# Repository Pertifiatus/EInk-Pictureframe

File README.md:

# E-Ink Picture Frame

A battery-powered **color e-paper picture frame** that rotates itself between portrait and landscape. Pictures are uploaded and managed in a web interface hosted by the frame itself.

## Features

- **7.3" Spectra 6 e-paper** (GDEP073E01, 800×480, 6 colors). It keeps the image without using power.
- **Motorized rotation:** a 28BYJ-48 stepper with a 40:1 worm gear turns the frame by 90°. An IMU (MPU-9250) detects the orientation and fine-tunes the position.
- **Built-in web app:** the frame opens its own WiFi access point (`http://192.168.4.1`) where you can:
  - upload and delete pictures (thumbnails are generated automatically)
  - create playlists and pick the current picture
  - set the clock, change settings, calibrate the motor
- **Deep sleep:** the DS3231 RTC wakes the frame to change the picture. A button wakes it up to start the WiFi interface.
- Battery monitoring with a low-battery indicator on the picture, plus an RGB status LED.
- Images, playlists and settings are stored on a microSD card.

## Hardware

| Part | Details |
|---|---|
| MCU | ESP32-S3 (with PSRAM) |
| Display | GDEP073E01 via DESPI-C02 adapter (SPI) |
| Storage | microSD (shares the SPI bus) |
| RTC / IMU | DS3231 + MPU-9250 (I2C) |
| Motor | 28BYJ-48 + ULN2003, worm gear 40:1 |
| Power | Li-ion battery |
| PCB | Custom KiCad board (`Ki-Cad/EInk-Rahmen`) |

All pins are defined in `config.h`.

## Repository structure

```
Arduino/
  eink_frame_V11/       Latest firmware (config.h, display/motor modules, web UI)
  eink_frame_V2..V10/   Earlier versions / milestones
  eink_frame_V10_WOmotor/  Variant without rotation motor
  Test/                 Hardware tests (display, SD, I2C scanner, LED, stepper)
3D Files/Frame.f3z      Fusion 360 frame model
Ki-Cad/EInk-Rahmen/     Schematic and PCB
```

## Getting started

1. Install these libraries: **GxEPD2**, **ESPAsyncWebServer** + **AsyncTCP** (mathieucarbou), **RTClib**, **AccelStepper**.
2. Board: *ESP32S3 Dev Module* with PSRAM enabled.
3. Copy `eink_frame.html` to the SD card as `/index.html` and create an `/images` folder.
4. Adjust the WiFi name/password in `config.h`, then upload `eink_frame_V11.ino`.
5. Press the WiFi button, connect to the frame's network and open `http://192.168.4.1`.

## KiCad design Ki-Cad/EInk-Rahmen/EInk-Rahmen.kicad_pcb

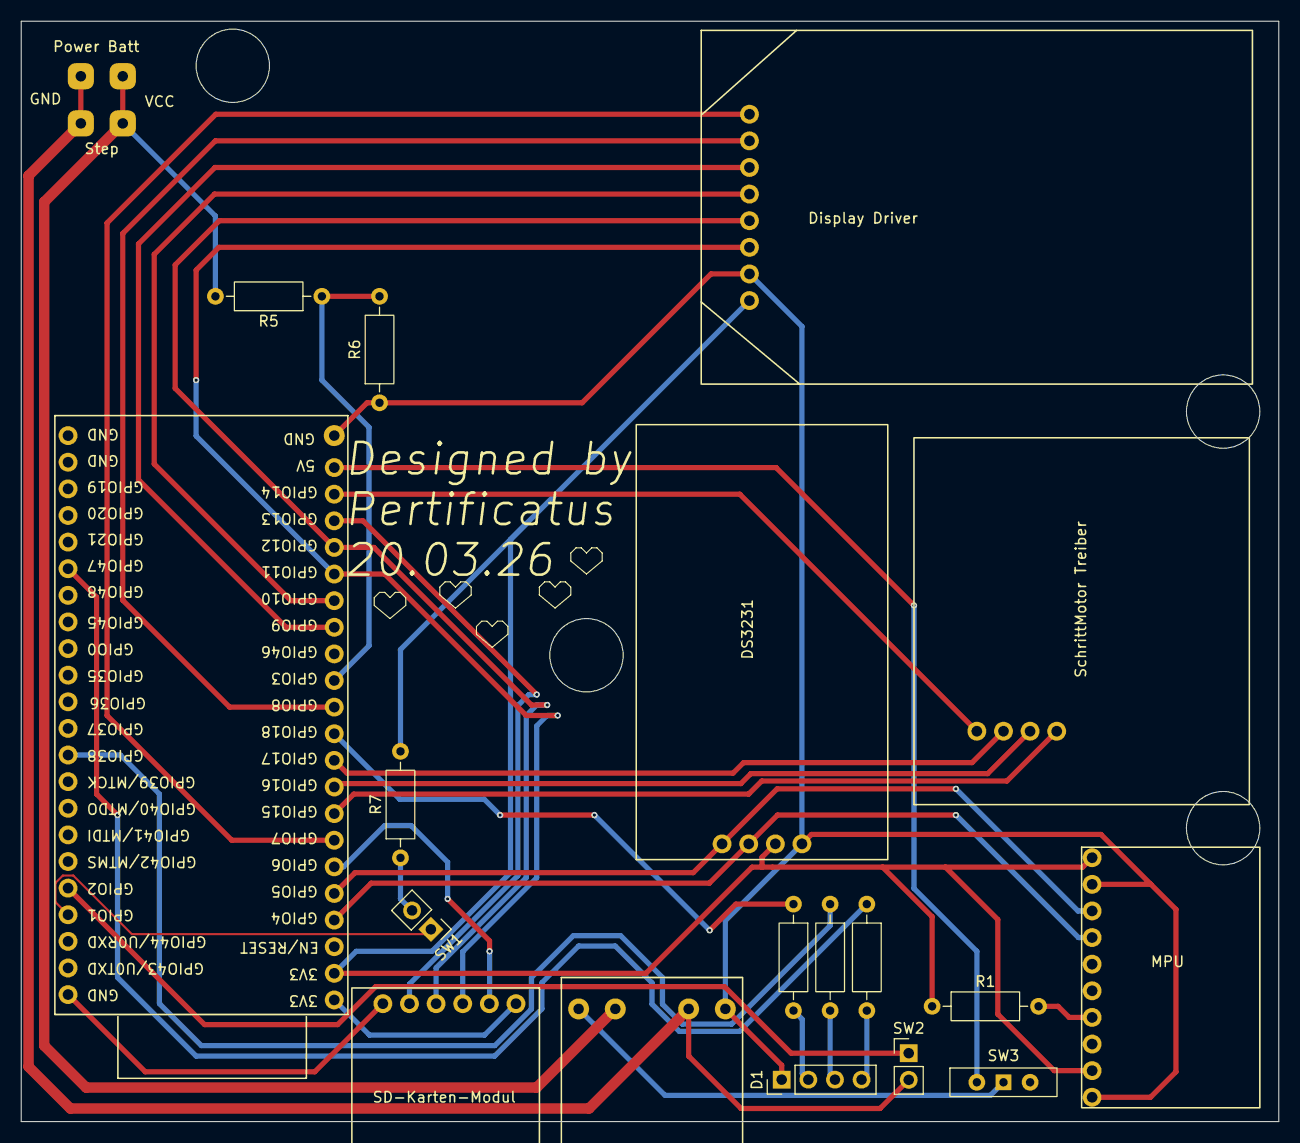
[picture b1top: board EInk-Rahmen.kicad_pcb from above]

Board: 2 copper layers, 120.0 x 105.0 mm, 19 parts (0 on the bottom side), 31 nets.

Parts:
D1: LED_ABGR; PinHeader_1x04_P2.54mm_Vertical
J1: Conn_01x04; Time Module
J2: Conn_01x10; MPU Modul
J3: Conn_01x06; SD Karten Modul
J4: Conn_01x08; Display Treiber
J5: Conn_01x04; Schrittmotor Treiber
J6: Conn_01x02; Power Management
R1, R7: 10k; R_Axial_DIN0207_L6.3mm_D2.5mm_P10.16mm_Horizontal
R2: R150; R_Axial_DIN0207_L6.3mm_D2.5mm_P10.16mm_Horizontal
R3, R4: R100; R_Axial_DIN0207_L6.3mm_D2.5mm_P10.16mm_Horizontal
R5, R6: 100k; R_Axial_DIN0207_L6.3mm_D2.5mm_P10.16mm_Horizontal
SW1: Kugelschalter; PinHeader_1x02_P2.54mm_Vertical
SW2: Wlan Taster; PinHeader_1x02_P2.54mm_Vertical
SW3: SW_Wuerth_450301014042; SW_Slide-03_Wuerth-WS-SLTV_10x2.5x6.4_P2.54mm
U1: ESP32-S3-DevKitC
U2: TP4056 USB-C Charging

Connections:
+4V: J6.1, R5.2, U2.2 (Battery_+)
GND: J6.2, SW2.2, U2.3 (Battery_-)
unnamed: D1.1 (A), J1.4, J2.2, J2.10, J3.6, J4.7, R6.1, U1.44 (GND), U2.4 (Out_-)
unnamed: D1.2 (BK), R4.2
unnamed: D1.3 (GK), R3.2
unnamed: D1.4 (RK), R2.2
unnamed: J1.1, J2.3, U1.5 (GPIO5/ADC1_CH4)
unnamed: J1.2, J2.4, U1.4 (GPIO4/ADC1_CH3)
unnamed: J1.3, J2.1, J2.9, J3.1, J4.8, R1.1, R7.2, U1.2 (3V3)
unnamed: J2.7, R1.2
unnamed: J3.2, U1.6 (GPIO6/ADC1_CH5)
unnamed: J3.3, J4.6, U1.17 (GPIO11/ADC2_CH0)
unnamed: J3.4, J4.5, U1.18 (GPIO12/ADC2_CH1)
unnamed: J3.5, U1.19 (GPIO13/ADC2_CH2)
unnamed: J4.1, U1.7 (GPIO7/ADC1_CH6)
unnamed: J4.2, U1.12 (GPIO8/ADC1_CH7)
unnamed: J4.3, U1.15 (GPIO9/ADC1_CH8)
unnamed: J4.4, U1.16 (GPIO10/ADC1_CH9)
unnamed: J5.1, U1.20 (GPIO14/ADC2_CH3)
unnamed: J5.2, U1.10 (GPIO17/ADC2_CH6)
unnamed: J5.3, U1.9 (GPIO16/ADC2_CH5/32K_N)
unnamed: J5.4, U1.8 (GPIO15/ADC2_CH4/32K_P)
unnamed: R7.1, SW1.2
unnamed: SW3.1 (B), U2.1 (Out_+)
unnamed: SW3.2 (C), U1.21 (5V)
unnamed: SW1.1, U1.41 (GPIO1/ADC1_CH0)
unnamed: SW2.1, U1.40 (GPIO2/ADC1_CH1)
unnamed: R5.1, R6.2, U1.13 (GPIO3/ADC1_CH2)
unnamed: R4.1, U1.11 (GPIO18/ADC2_CH7)
unnamed: R3.1, U1.35 (GPIO38)
unnamed: R2.1, U1.28 (GPIO47)
